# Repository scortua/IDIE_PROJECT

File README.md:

#### Diseño de un Sistema de Monitoreo de Vibraciones IoT con Conectividad LoRaWAN
# PROYECTO INTEGRACIÓN DISPOSITIVOS ELECTRÓNICOS

## Índice
* [PCB](#diseño-pcb)
* [3D](#diseño-3d)

## Entregables del Proyecto

### Entregable 1: Documentación Técnica y Conceptual
La guía se encuentra en el archivo _Markdown_ [Base entregable 1](./ent1.md) y abarca:
- **Introducción:** Presentación del proyecto, la motivación y los objetivos.
- **Detalle del Producto:** Especificaciones técnicas, características físicas y funcionales del dispositivo IoT.
- **Alcance de los Servicios Ofertados:** Descripción de los servicios incluidos, como el diseño de hardware, firmware, pruebas y documentación completa.
- **Exclusiones del Alcance:** Elementos y servicios que no se consideran en el proyecto (producción en masa, logística, etc.).
- **Valor:** Análisis de costos, desglose de inversión y metodologías de cálculo.
- **Cronograma de Trabajo:** Fases del proyecto y tiempo estimado para cada etapa.
- **Tiempo de Entrega:** Fechas clave y plazos para los entregables parciales y finales.

---

### Entregable 2: Diseño y Sustentación Técnica
Disponible en el archivo _Markdown_ [Base entregable 2](./ent2.md), este entregable se compone de:
- **Sustentación del Diseño:** Presentación y defensa del diseño, representando un 30% de la evaluación.
- **Informe Digital Detallado (35%):**
  - Descripción general de la solución y su justificación.
  - Diagramas de bloques que ilustren el flujo y la estructura de la solución.
  - Descripción detallada de cada bloque (funciones y relaciones).
  - Relación entre la solución y los requerimientos solicitados.
  - Especificaciones técnicas de los componentes electrónicos clave (MCU, memorias, fuentes, interfaces, etc.).
  - Diseño esquemático del sistema.
  - Diseño de PCB, presentando cada capa (máscara de componentes, anti-soldadura, crema, cobre y perforaciones).
  - Lista de materiales (BOM List).
  - Modelo 3D del producto final.
  - Cuadro de costos de producción para diferentes volúmenes (1, 10, 100, 500, 1000 y 5000 unidades).
- **Paquete Digital Adicional (35%):**
  - Informe en PDF con toda la documentación.
  - Archivo PDF del esquemático.
  - Archivos GERBER del diseño de la PCB.
  - Archivo BOM en Excel.
  - Archivo STEP o STL del modelo 3D.
  - Hoja de cálculo para el cuadro de costos, con fórmula automática según la cantidad a producir.
  - Hojas de datos (datasheets) de los componentes principales.

---

### Entregable 3: Manuales, Brochure y Prototipo Final
La guía se encuentra en [Base entregable 3](./ent3.md) y comprende:
- **Manual de Usuario:** Documento PDF que explica el funcionamiento y manejo del dispositivo (10%).
- **Brochure del Producto:** Ficha comercial en PDF que resalta las ventajas competitivas y características principales (10%).
- **Informe Digital Actualizado (20%):**
  - Descripción del firmware desarrollado y su funcionamiento.
  - Diagrama de flujo de la aplicación.
  - Detalle de los drivers implementados.
  - Retos y dificultades enfrentadas junto con las soluciones aplicadas.
  - Conclusiones finales y lecciones aprendidas.
  - Inclusión y actualización del paquete digital definido en el Entregable 2.
- **Prototipo Final Funcional:** Durante la presentación, se evaluarán todas las características y funcionalidades estipuladas en el proyecto (60%).

Cada uno de estos entregables está diseñado para garantizar una documentación integral y una validación exhaustiva del proyecto, cubriendo desde la concepción de la idea hasta la demostración práctica del sistema IoT.

# DISEÑO GENERAL
Antes de comenzar es necesario buscar sobre dispositivos similares y si existen, toda la idea de los componentes principales que tienen sus características principales en el diseño y después los requeridos para el funcionamiento de lo necesario.

## Diseño PCB

<details>
<summary> Dimensiones </summary>
Primer paso fue construir la PCB que entrara a la perfección dentro de la caja seleccionada que se ve a continuación.

Estas medidas se siguieron al pie de la letra para poder diseñar a la perfección la PCB y el circuito que se desea.
</details>

## Componentes
#### Componentes Usados

A continuación se describen los dispositivos fundamentales utilizados en el proyecto, documentados en los archivos PDF disponibles:

- **Socket Batería:** ([1015-socketbattery.pdf](./Documentos/1015-socketbattery.pdf))  
  Se especifica el diseño del conector para integración segura y confiable del paquete de alimentación.

- **Cristal Oscilador:** ([ABS06-cristal.pdf](./Documentos/ABS06-cristal.pdf))  
  Fundamental para la sincronización de circuitos, garantizando estabilidad y precisión en el reloj del sistema.

- **Bobina y Núcleo de Ferrita:** ([core_ferrita-coil.pdf](./Documentos/core_ferrita-coil.pdf))  
  Componentes críticos en la filtración y manejo de interferencias electromagnéticas en el circuito.

- **Convertidor Serial:** ([DS_FT234XD-serialconverter.pdf](./Documentos/DS_FT234XD-serialconverter.pdf))  
  Facilita la comunicación entre el microcontrolador y dispositivos externos mediante interfaces USB y serie.

- **Unidad de Medición Inercial (IMU):** ([FXLS8974CFR3-imu.pdf](./Documentos/FXLS8974CFR3-imu.pdf))  
  Incorpora sensores que permiten la detección y el análisis de movimientos y vibraciones, contribuyendo a la monitorización del estado del dispositivo.

- **Sensor de Efecto Hall:** ([hall_efect-sensor.pdf](./Documentos/hall_efect-sensor.pdf))  
  Utilizado para detectar cambios en campos magnéticos, lo que aporta datos relevantes en aplicaciones de control de propiedad magnética.

- **LED RGB:** ([HB_CLY6D-rgb_led.pdf](./Documentos/HB_CLY6D-rgb_led.pdf))  
  Proporciona indicadores visuales para el estado del sistema, útil para diagnósticos o notificaciones.

- **Módulo LoRa:** ([LoRa_E5_module.pdf](./Documentos/LoRa_E5_module.pdf))  
  Es el componente clave para la conexión IoT a través de la red LoRaWAN, permitiendo la transmisión de datos a larga distancia.

- **Transistor y MOSFET:** ([transistor.pdf](./Documentos/transistor.pdf), [SI2305B_SOT_23-mosfet.pdf](./Documentos/SI2305B_SOT_23-mosfet.pdf))  
  Empleados para la gestión de señales y el control de potencia dentro del circuito integrado.

- **Microcontrolador:** ([stm32l071v8-micro.pdf](./Documentos/stm32l071v8-micro.pdf))  
  El cerebro del sistema, encargado de coordinar las comunicaciones, procesar las señales de los sensores y gestionar las acciones del dispositivo.

- **Protección de Diodos:** ([usblc6_2SY6-diode-protection.pdf](./Documentos/usblc6_2SY6-diode-protection.pdf))  
  Asegura la integridad del circuito frente a sobretensiones y otros picos de corriente, protegiendo los componentes sensibles.

- **Antena:** ([W2311-antenna.pdf](./Documentos/W2311-antenna.pdf))
  La antena es un componente crítico en la conexión IoT a través de LoRaWAN. Su función es asegurar una comunicación fiable y de largo alcance al transmitir y recibir datos en frecuencias específicas.
  - **Tipo:** Diseñada para ser compacta y eficiente, comúnmente usando tecnología PCB o de hilo.
  - **Frecuencia Operativa:** Se adapta a bandas como 433 MHz, 868 MHz o 915 MHz, según las normativas locales.
  - **Ganancia y Eficiencia:** Optimizada para maximizar el alcance y garantizar una recepción estable.

## Esquemático
### Desarrollo del Esquemático

Para el desarrollo del esquemático se utilizó el software Eagle, lo que permitió integrar de forma precisa todos los elementos del circuito. Los componentes se seleccionaron desde Mouser y se incorporaron mediante el gestor de librerías Library Loader, asegurando una integración coherente y validada antes de avanzar al diseño de PCB.
Para la hoja 1 se tiene:

Y para la hoja 2 se tiene:

## PCB
Ahora, con el diseño del esquemático como se planteo es construirlo en un modelo de caja

## Diseño 3D

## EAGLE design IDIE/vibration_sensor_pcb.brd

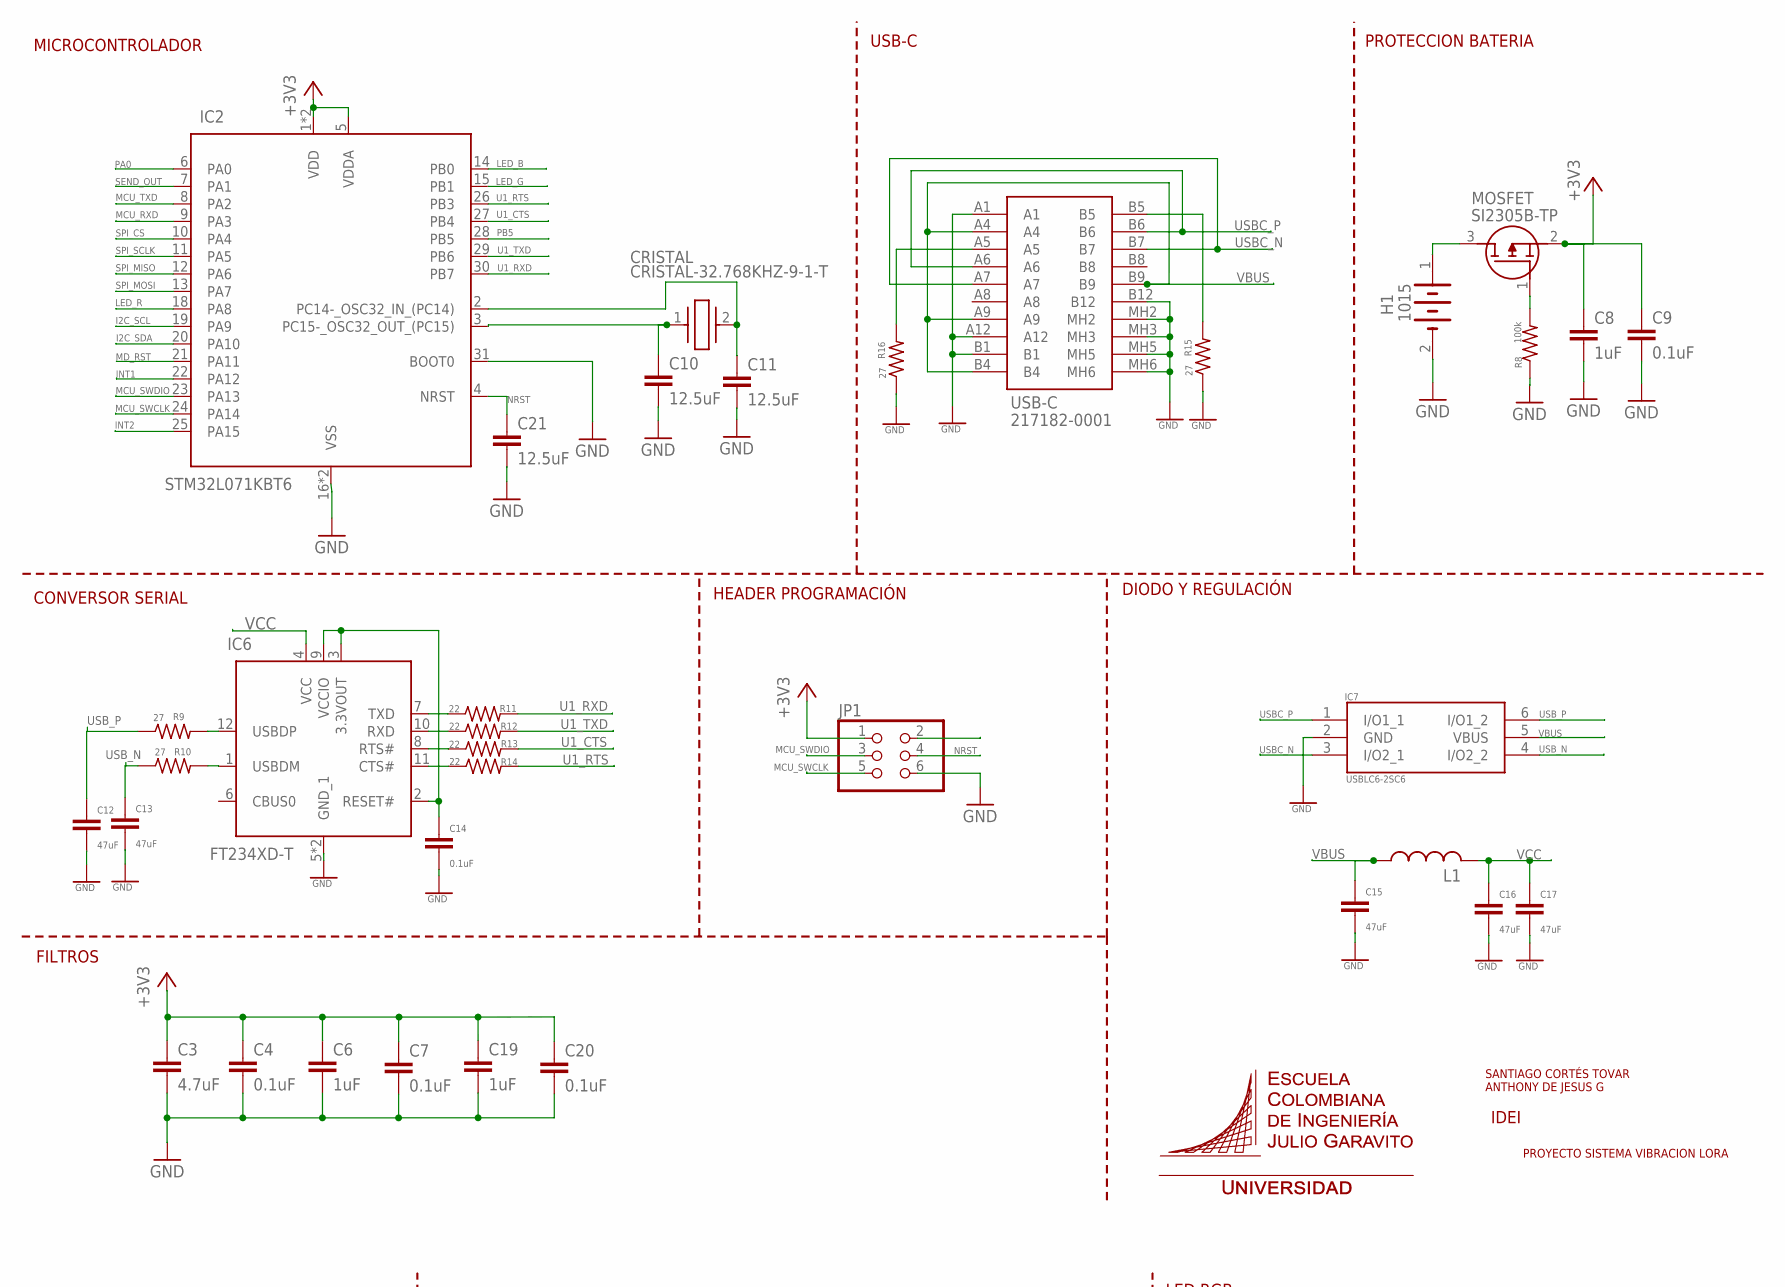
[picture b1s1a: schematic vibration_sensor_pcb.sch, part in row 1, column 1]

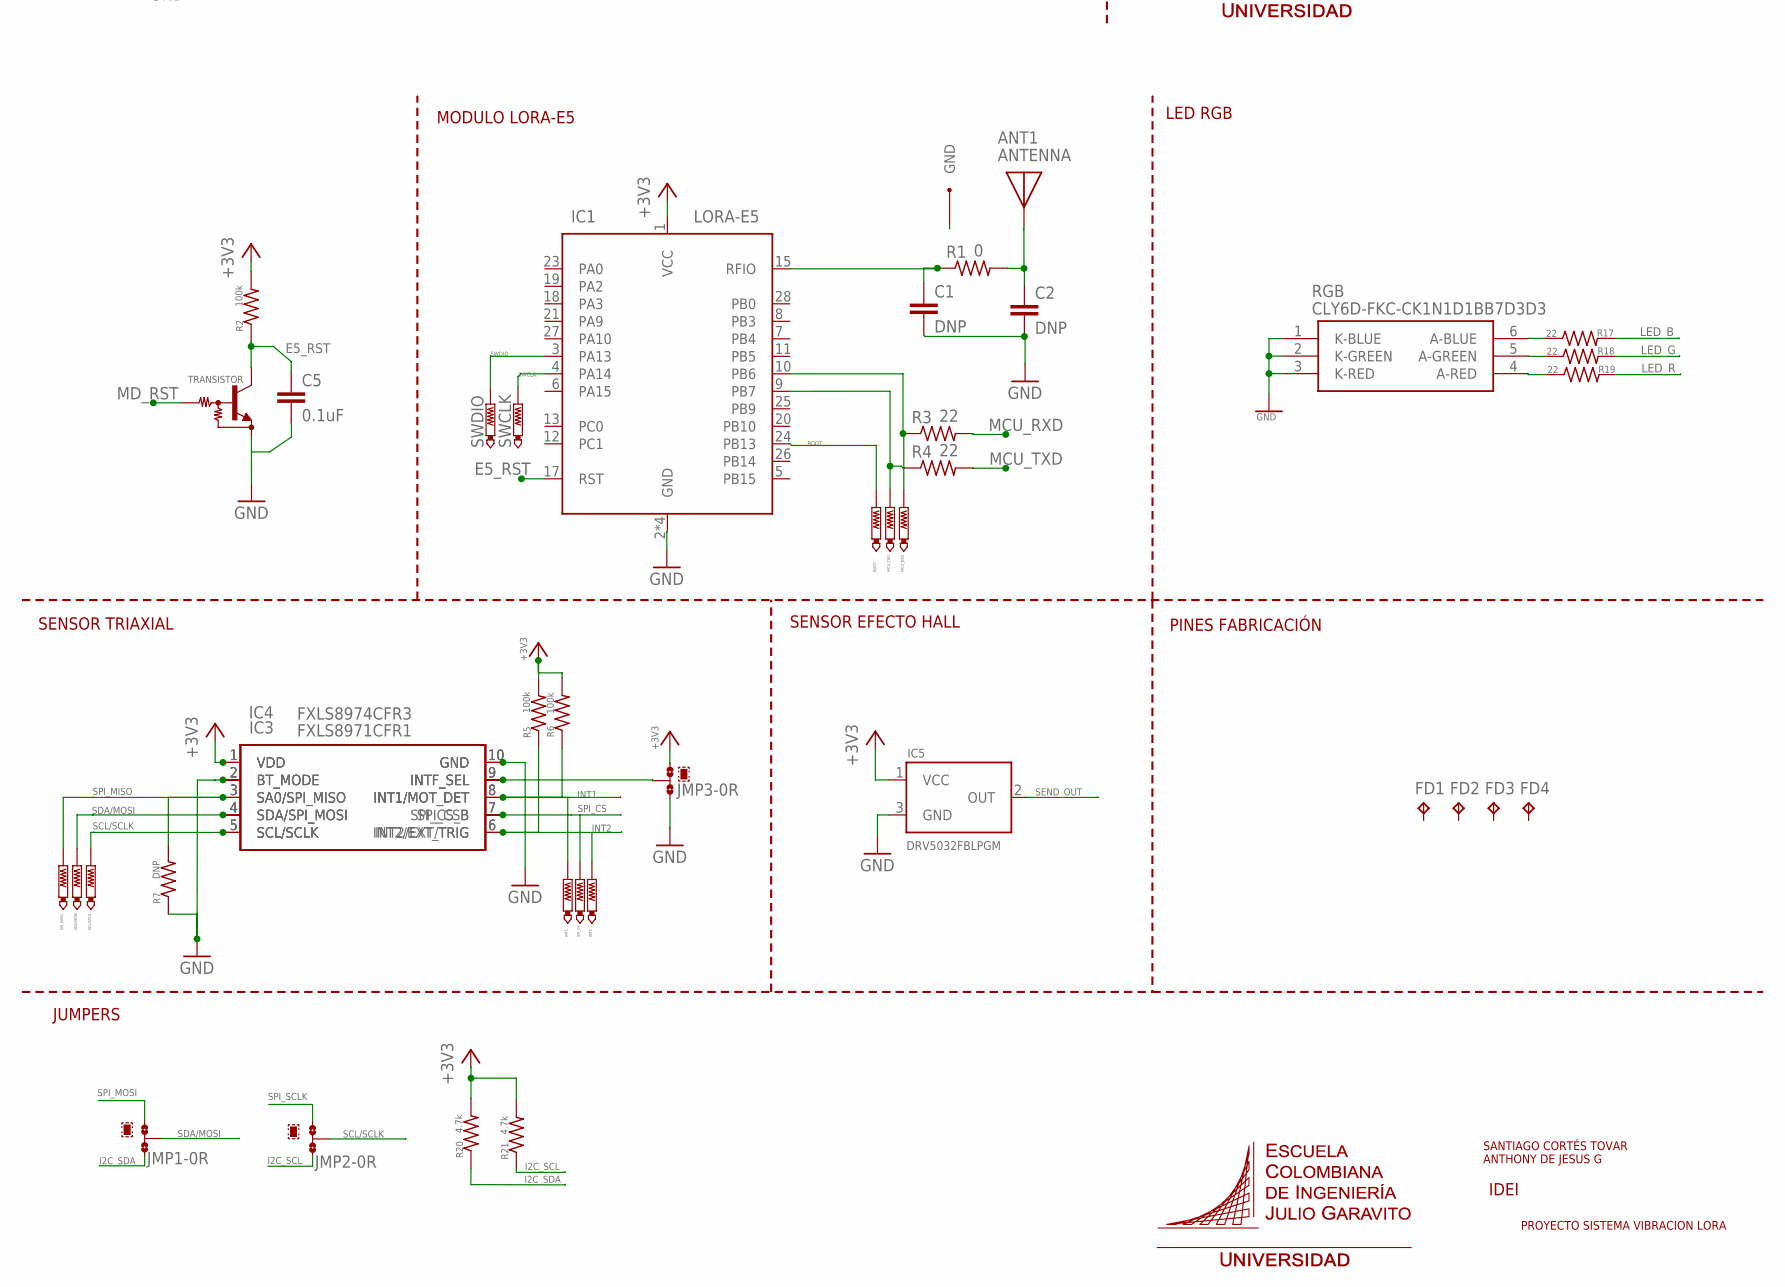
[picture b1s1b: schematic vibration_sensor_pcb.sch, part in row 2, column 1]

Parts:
ANT1: ANTENNA
BOOT: PTR1TP11R; TP11R
C1, C2: DNP; C0603
C3: 4.7uF; C0603
C4, C5, C7, C9, C14, C20: 0.1uF; C0603
C6, C8, C19: 1uF; C0603
C10, C11, C21: 12.5uF; C0603
C12, C13, C15, C16, C17: 47uF; C0603
CRISTAL: CRISTAL-32.768KHZ-9-1-T; CRISTAL-32.768
FD1, FD2, FD3, FD4: TPTP10R; TP10R
H1: 1015
IC1: LORA-E5
IC2: STM32L071KBT6
IC3: FXLS8974CFR3
IC4: FXLS8971CFR1
IC5: DRV5032FBLPGM; SOT23
IC6: FT234XD-T; SON45P300X300X80-13N
IC7: USBLC6-2SC6; SOT95P280X145-6N
INT1, INT2: PTR1TP11R; TP11R
JMP1, JMP2, JMP3: 0R-JUMPA; A0R-JMP
JP1: PINHD-2X3; 2X03
L1: L-US; C0805K
MCU_RXD: PTR1TP11R; TP11R
MCU_TXD: PTR1TP11R; TP11R
MOSFET: SI2305B-TP; SOT95P237X125-3N
R1: 0; R0603
R2, R5, R6, R8: 100k; R0603
R3, R4, R11, R12, R13, R14, R17, R18, R19: 22; R0603
R7: DNP; R0603
R9, R10, R15, R16: 27; R0603
R20, R21: 4.7k; R0603
RGB: CLY6D-FKC-CK1N1D1BB7D3D3; PLCC6
SCL/SCLK: PTR1TP11R; TP11R
SDA/MOSI: PTR1TP11R; TP11R
SPI_CS: PTR1TP11R; TP11R
SPI_MISO: PTR1TP11R; TP11R
SWCLK: PTR1TP11R; TP11R
SWDIO: PTR1TP11R; TP11R
TRANSISTOR: MUN2211T1-NPN_DRIVER-SC59-BEC; SC59-BEC
USB-C: 217182-0001; 2171820001

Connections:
+3V3: C3.1, C4.1, C6.1, C7.1, C8.1, C9.1, C19.1, C20.1, IC1.1 (VCC), IC2.1 (VDD), IC2.5 (VDDA), IC2.17 (VDD), IC3.1 (VDD), IC4.1 (VDD), IC5.1 (VCC), JMP3.3, JP1.1, MOSFET.2 (S), R2.2, R5.2, R6.2, R20.2, R21.2
A5: R16.2, USB-C.A5
ANT: ANT1.1 (FEED), C2.1, R1.2
B5: R15.2, USB-C.B5
BOOT: BOOT.TP, IC1.24 (PB13)
E5_RST: C5.1, IC1.17 (RST), R2.1, TRANSISTOR.C
GATE: MOSFET.1 (G), R8.2
GND: ANT1.2 (GND), ANT1.3 (GND), C1.2, C2.2, C3.2, C4.2, C5.2, C6.2, C7.2, C8.2, C9.2, C10.2, C11.2, C12.2, C13.2, C14.2, C15.2, C16.2, C17.2, C19.2, C21.2, H1.2 (-), IC1.2 (GND), IC1.14 (GND), IC1.16 (GND), IC1.22 (GND), IC2.16 (VSS), IC2.31 (BOOT0), IC2.32 (VSS), IC3.2 (BT_MODE), IC3.10 (GND), IC4.2 (BT_MODE), IC4.10 (GND), IC5.3 (GND), IC6.5 (GND_1), IC6.13 (GND_1), IC7.2 (GND), JMP3.1, JP1.6, R7.1, R8.1, R15.1, R16.1, RGB.1 (K-BLUE), RGB.2 (K-GREEN), RGB.3 (K-RED), TRANSISTOR.E, USB-C.A1, USB-C.A12, USB-C.B1, USB-C.B12, USB-C.MH2, USB-C.MH3, USB-C.MH5, USB-C.MH6
GND1: C20.2
I2C_SCL: IC2.19 (PA9), JMP2.3, R21.1
I2C_SDA: IC2.20 (PA10), JMP1.3, R20.1
INT1: IC2.22 (PA12), IC3.8 (INT1/MOT_DET), IC4.8 (INT1/MOT_DET), INT1.TP, R6.1
INT2: IC2.25 (PA15), IC3.6 (INT2/EXT_TRIG), IC4.6 (INT2/EXT/TRIG), INT2.TP, R5.1
INTF_SEL: IC3.9 (INTF_SEL), IC4.9 (INTF_SEL), JMP3.2
IN_MOSFET: H1.1 (+), MOSFET.3 (D)
LED_B: IC2.14 (PB0), R17.2
LED_G: IC2.15 (PB1), R18.2
LED_R: IC2.18 (PA8), R19.2
LORA_RXD: IC1.10 (PB6), MCU_RXD.TP, R3.1
LORA_TXD: IC1.9 (PB7), MCU_TXD.TP, R4.1
MCU_RXD: IC2.9 (PA3), R3.2
MCU_SWCLK: IC2.24 (PA14), JP1.5
MCU_SWDIO: IC2.23 (PA13), JP1.3
MCU_TXD: IC2.8 (PA2), R4.2
MD_RST: IC2.21 (PA11), TRANSISTOR.B
NRST: C21.1, IC2.4 (NRST), JP1.4
OSC32_IN: C11.1, CRISTAL.2, IC2.2 (PC14-_OSC32_IN_(PC14))
OSC32_OUT: C10.1, CRISTAL.1, IC2.3 (PC15-_OSC32_OUT_(PC15))
OUT_ANT: C1.1, IC1.15 (RFIO), R1.1
PA0: IC2.6 (PA0)
PB5: IC2.28 (PB5)
R11: IC6.7 (TXD), R11.1
R12: IC6.10 (RXD), R12.1
R13: IC6.8 (RTS#), R13.1
R14: IC6.11 (CTS#), R14.1
R17: R17.1, RGB.6 (A-BLUE)
R18: R18.1, RGB.5 (A-GREEN)
R19: R19.1, RGB.4 (A-RED)
RESET#: C14.1, IC6.2 (RESET#), IC6.3 (3.3VOUT), IC6.9 (VCCIO)
SCL/SCLK: IC3.5 (SCL/SCLK), IC4.5 (SCL/SCLK), JMP2.2, SCL/SCLK.TP
SDA/MOSI: IC3.4 (SDA/SPI_MOSI), IC4.4 (SDA/SPI_MOSI), JMP1.2, SDA/MOSI.TP
SEND_OUT: IC2.7 (PA1), IC5.2 (OUT)
SPI_CS: IC2.10 (PA4), IC3.7 (SPI_CS_B), IC4.7 (SPI_CSB), SPI_CS.TP
SPI_MISO: IC2.12 (PA6), IC3.3 (SA0/SPI_MISO), IC4.3 (SA0/SPI_MISO), R7.2, SPI_MISO.TP
SPI_MOSI: IC2.13 (PA7), JMP1.1
SPI_SCLK: IC2.11 (PA5), JMP2.1
SWCLK: IC1.4 (PA14), SWCLK.TP
SWDIO: IC1.3 (PA13), SWDIO.TP
U1_CTS: IC2.27 (PB4), R13.2
U1_RTS: IC2.26 (PB3), R14.2
U1_RXD: IC2.30 (PB7), R11.2
U1_TXD: IC2.29 (PB6), R12.2
USBC_N: IC7.3 (I/O2_1), USB-C.A7, USB-C.B7
USBC_P: IC7.1 (I/O1_1), USB-C.A6, USB-C.B6
USBDM: IC6.1 (USBDM), R10.2
USBDP: IC6.12 (USBDP), R9.2
USB_N: C13.1, IC7.4 (I/O2_2), R10.1
USB_P: C12.1, IC7.6 (I/O1_2), R9.1
VBUS: C15.1, IC7.5 (VBUS), L1.1, USB-C.A4, USB-C.A9, USB-C.B4, USB-C.B9
VCC: C16.1, C17.1, IC6.4 (VCC), L1.2

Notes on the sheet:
IDEI
SANTIAGO CORTÉS TOVAR ANTHONY DE JESUS G
PROYECTO SISTEMA VIBRACION LORA
MICROCONTROLADOR
USB-C
PROTECCION BATERIA
CONVERSOR SERIAL
HEADER PROGRAMACIÓN
DIODO Y REGULACIÓN
MODULO LORA-E5
LED RGB
SENSOR TRIAXIAL
SENSOR EFECTO HALL
PINES FABRICACIÓN
JUMPERS
FILTROS

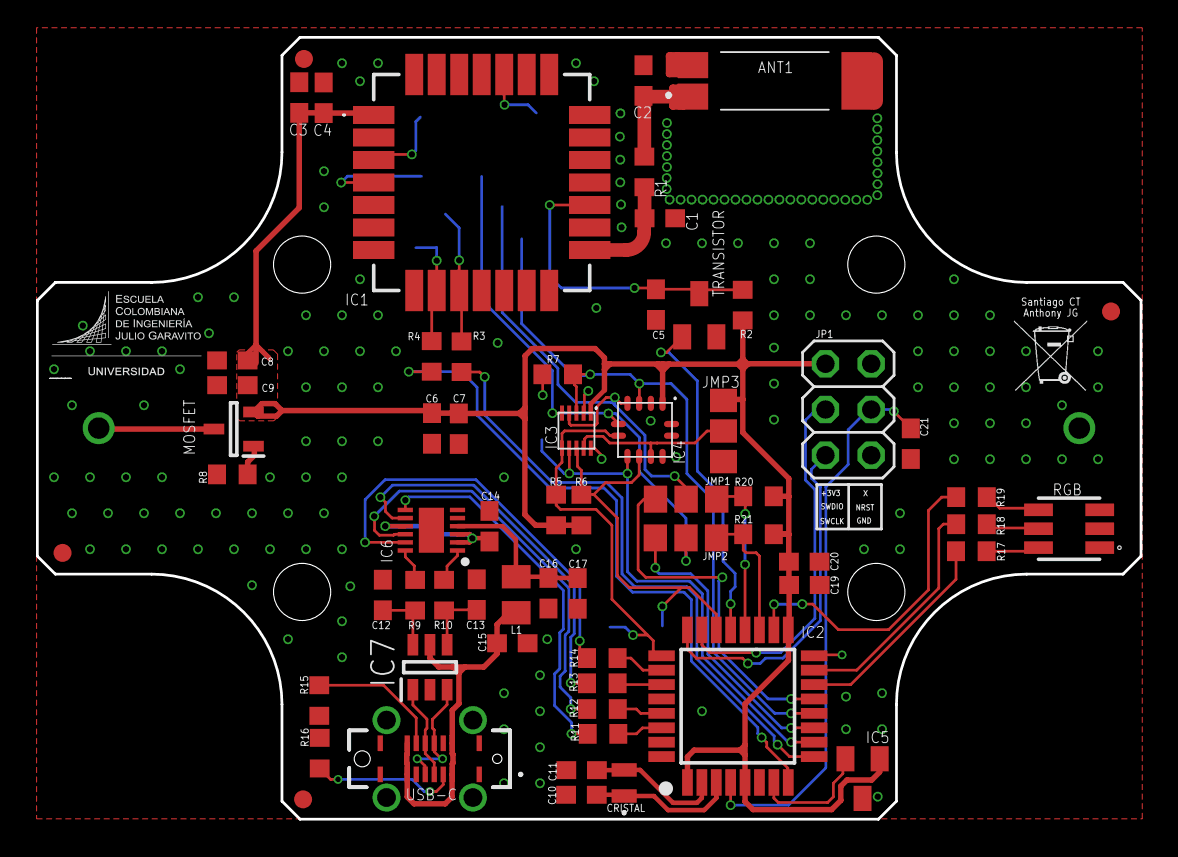
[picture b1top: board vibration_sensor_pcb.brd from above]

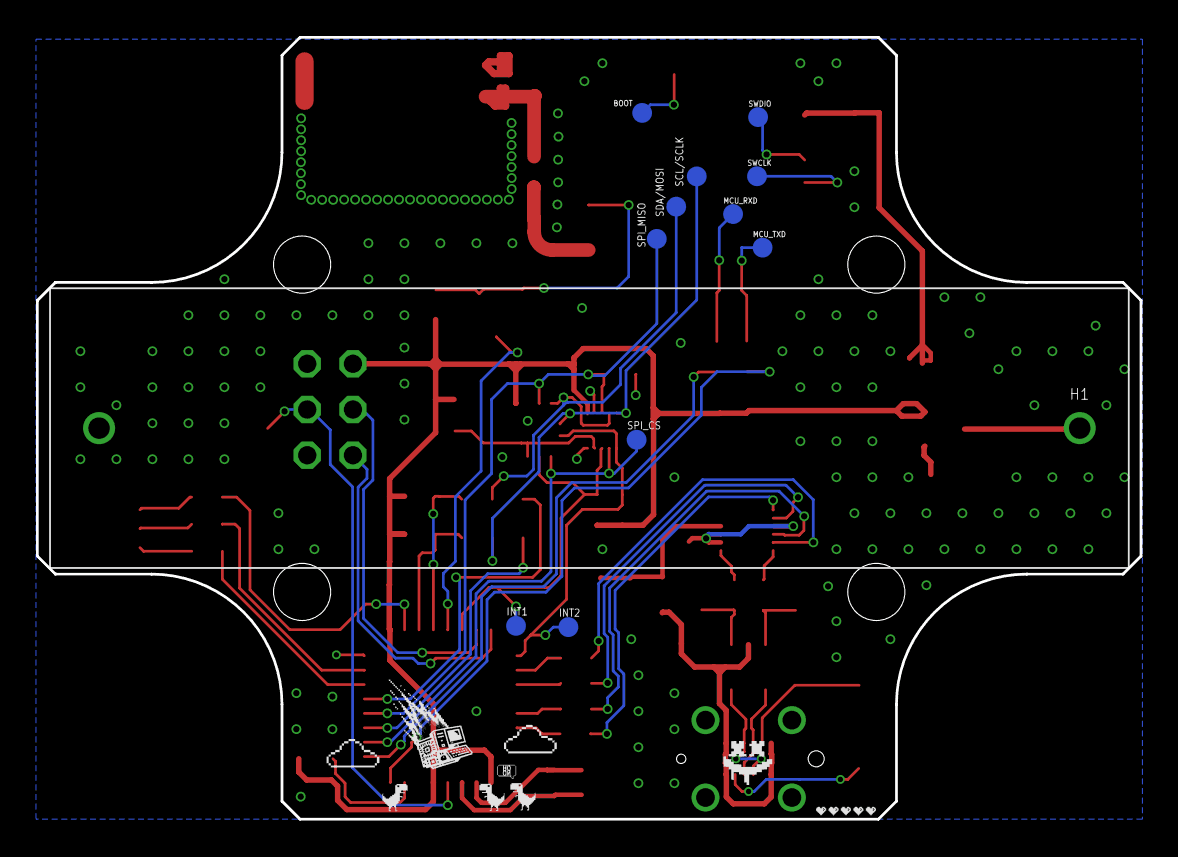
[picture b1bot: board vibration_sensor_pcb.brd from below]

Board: 2 copper layers, 61.3 x 43.4 mm, 75 parts (12 on the bottom side), 57 nets.

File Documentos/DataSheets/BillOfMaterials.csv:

"Qty";"Value";"Device";"Package";"Parts";"Description";"ARROW_PART_NUMBER";"ARROW_PRICE-STOCK";"DESCRIPTION";"HEIGHT";"MANUFACTURER_NAME";"MANUFACTURER_PART_NUMBER";"MOUSER_PART_NUMBER";"MOUSER_PRICE-STOCK";"POPULARITY";"SPICEPREFIX";"TP_SIGNAL_NAME";
"1";"";"L-US";"C0805K";"L1";"INDUCTOR, American symbol";"";"";"";"";"";"";"";"";"";"";"";
"1";"";"MUN2211T1-NPN_DRIVER-SC59-BEC";"SC59-BEC";"TRANSISTOR";"NPN Bias Resistor Transistor";"";"";"";"";"";"";"";"";"0";"J";"";
"1";"";"PINHD-2X3";"2X03";"JP1";"PIN HEADER";"";"";"";"";"";"";"";"";"62";"";"";
"1";"0";"R-US_R0603";"R0603";"R1";"RESISTOR, American symbol";"";"";"";"";"";"";"";"";"77";"R";"";
"6";"0.1uF";"C-EUC0603";"C0603";"C4, C5, C7, C9, C14, C20";"CAPACITOR, European symbol";"";"";"";"";"";"";"";"";"73";"C";"";
"3";"0R-JUMPA";"0R-JUMPA";"A0R-JMP";"JMP1, JMP2, JMP3";"SMD 0R 0805 Jumper";"";"";"";"";"";"";"";"";"3";"";"";
"4";"100k";"R-US_R0603";"R0603";"R2, R5, R6, R8";"RESISTOR, American symbol";"";"";"";"";"";"";"";"";"77";"R";"";
"1";"1015";"1015";"1015";"H1";"Cylindrical Battery Contacts, Clips, Holders & Springs AA PC Battery HOLDER";"";"";"Cylindrical Battery Contacts, Clips, Holders & Springs AA PC Battery HOLDER";"mm";"Keystone Electronics";"1015";"534-1015";"https://www.mouser.co.uk/ProductDetail/Keystone-Electronics/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";"";"";"";
"3";"12.5uF";"C-EUC0603";"C0603";"C10, C11, C21";"CAPACITOR, European symbol";"";"";"";"";"";"";"";"";"73";"C";"";
"3";"1uF";"C-EUC0603";"C0603";"C6, C8, C19";"CAPACITOR, European symbol";"";"";"";"";"";"";"";"";"73";"C";"";
"1";"217182-0001";"217182-0001";"2171820001";"USB-C";"USB-C,VERT SMT,16P 6.40mm HT";"";"";"USB-C,VERT SMT,16P 6.40mm HT";"7.6mm";"Molex";"217182-0001";"538-217182-0001";"https://www.mouser.co.uk/ProductDetail/Molex/217182-0001?qs=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";"";"";"";
"9";"22";"R-US_R0603";"R0603";"R3, R4, R11, R12, R13, R14, R17, R18, R19";"RESISTOR, American symbol";"";"";"";"";"";"";"";"";"77";"R";"";
"4";"27";"R-US_R0603";"R0603";"R9, R10, R15, R16";"RESISTOR, American symbol";"";"";"";"";"";"";"";"";"77";"R";"";
"2";"4.7k";"R-US_R0603";"R0603";"R20, R21";"RESISTOR, American symbol";"";"";"";"";"";"";"";"";"77";"R";"";
"1";"4.7uF";"C-EUC0603";"C0603";"C3";"CAPACITOR, European symbol";"";"";"";"";"";"";"";"";"73";"C";"";
"5";"47uF";"C-EUC0603";"C0603";"C12, C13, C15, C16, C17";"CAPACITOR, European symbol";"";"";"";"";"";"";"";"";"73";"C";"";
"1";"ANTENNA";"ANTENNA";"ANTENNA";"ANT1";"PULSE LARSEN ANTENNAS - W3211 - CERAMIC ON GROUND ANTENNA, 902-928MHZ";"";"";"PULSE LARSEN ANTENNAS - W3211 - CERAMIC ON GROUND ANTENNA, 902-928MHZ";"5mm";"Pulse Electronics";"W3211";"673-W3211";"https://www.mouser.co.uk/ProductDetail/PulseLarsen-Antennas/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";"";"";"";
"1";"CLY6D-FKC-CK1N1D1BB7D3D3";"CLY6D-FKC-CK1N1D1BB7D3D3";"PLCC6";"RGB";"LED  Blue/Green/Red 6-Pin PLCC T/R Cree CLY6D-FKC-CK1N1D1BB7D3D3, CLY6D-FKC Series RGB LED, 480 (Blue) nm, 540 (Green) nm, 624 (Red) nm PLCC 6";"";"";"LED  Blue/Green/Red 6-Pin PLCC T/R Cree CLY6D-FKC-CK1N1D1BB7D3D3, CLY6D-FKC Series RGB LED, 480 (Blue) nm, 540 (Green) nm, 624 (Red) nm PLCC 6";"mm";"CREE LED";"CLY6D-FKC-CK1N1D1BB7D3D3";"941-CLY6DFKCCK1N1D1B";"https://www.mouser.co.uk/ProductDetail/Cree-LED/CLY6D-FKC-CK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";"";"";"";
"1";"CRISTAL-32.768KHZ-9-1-T";"CRISTAL-32.768KHZ-9-1-T";"CRISTAL-32.768";"CRISTAL";"ABRACON - ABS06-32.768KHZ-9-1-T - CRYSTAL, 32.768KHZ, 9PF, 2 X 1.2MM";"";"";"ABRACON - ABS06-32.768KHZ-9-1-T - CRYSTAL, 32.768KHZ, 9PF, 2 X 1.2MM";"0.6mm";"ABRACON";"ABS06-32.768KHZ-9-1-T";"815-ABS06-32.7K-9-T";"https://www.mouser.co.uk/ProductDetail/ABRACON/ABS06-32.768K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";"";"";"";
"2";"DNP";"C-EUC0603";"C0603";"C1, C2";"CAPACITOR, European symbol";"";"";"";"";"";"";"";"";"73";"C";"";
"1";"DNP";"R-US_R0603";"R0603";"R7";"RESISTOR, American symbol";"";"";"";"";"";"";"";"";"77";"R";"";
"1";"DRV5032FBLPGM";"DRV5032FBLPGM";"SOT23";"IC5";"";"";"";"";"";"";"";"";"";"";"";"";
"1";"FT234XD-T";"FT234XD-T";"SON45P300X300X80-13N";"IC6";"USB Interface IC USB to Basic Serial UART IC";"";"";"USB Interface IC USB to Basic Serial UART IC";"0.8mm";"FTDI(Future Designs)";"FT234XD-T";"";"";"";"";"";
"1";"FXLS8971CFR1";"FXLS8971CFR1";"FXLS8971CFR1";"IC4";"3-Axis Low-g Accelerometer FXLS8971CF is available in a 3 mm x 3 mm x 1.25 mm 12-pin QFN package with 0.65 mm pitch and wettable flanks";"";"";"3-Axis Low-g Accelerometer FXLS8971CF is available in a 3 mm x 3 mm x 1.25 mm 12-pin QFN package with 0.65 mm pitch and wettable flanks";"1.3mm";"NXP";"FXLS8971CF";"";"";"";"";"";
"1";"FXLS8974CFR3";"FXLS8974CFR3";"FXLS8974CFR3";"IC3";"Accelerometer X, Y, Z Axis +/-2g, 4g, 8g, 16g 1.6kHz 10-DFN (2x2)";"";"";"Accelerometer X, Y, Z Axis +/-2g, 4g, 8g, 16g 1.6kHz 10-DFN (2x2)";"1mm";"NXP";"FXLS8974CFR3";"771-FXLS8974CFR3";"https://www.mouser.co.uk/ProductDetail/NXP-Semiconductors/FX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";"";"";"";
"1";"LORA-E5";"LORA-E5";"LORA-E5";"IC1";"Sub-GHz Modules LoRa-E5 Wireless Module LoRa-E5 has a 28-pin SMD package";"";"";"Sub-GHz Modules LoRa-E5 Wireless Module LoRa-E5 has a 28-pin SMD package";"2.5mm";"Seeed Studio";"317990687";"713-317990687";"https://www.mouser.co.uk/ProductDetail/Seeed-Studio/31799068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";"";"";"";
"11";"PTR1TP11R";"PTR1TP11R";"TP11R";"BOOT, INT1, INT2, MCU_RXD, MCU_TXD, SCL/SCLK, SDA/MOSI, SPI_CS, SPI_MISO, SWCLK, SWDIO";"TEST PIN";"";"";"";"";"";"";"";"";"1";"";"";
"1";"SI2305B-TP";"SI2305B-TP";"SOT95P237X125-3N";"MOSFET";"P-Channel 20 V 4.2A (Tj) 1.4W Surface Mount SOT-23";"";"";"P-Channel 20 V 4.2A (Tj) 1.4W Surface Mount SOT-23";"1.25mm";"MCC";"SI2305B-TP";"833-SI2305B-TP";"https://www.mouser.co.uk/ProductDetail/Micro-Commercial-Comp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";"";"";"";
"1";"STM32L071KBT6";"STM32L071KBT6";"STM32L071KBT6";"IC2";"MCU 32-bit STM32 ARM Cortex M0+ RISC 128KB Flash 2.5V/3.3V 32-Pin LQFP Tray";"";"";"MCU 32-bit STM32 ARM Cortex M0+ RISC 128KB Flash 2.5V/3.3V 32-Pin LQFP Tray";"1.6mm";"STMicroelectronics";"STM32L071KBT6";"511-STM32L071KBT6";"https://www.mouser.co.uk/ProductDetail/STMicroelectronics/ST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";"";"";"";
"4";"TPTP10R";"TPTP10R";"TP10R";"FD1, FD2, FD3, FD4";"Test pad";"";"";"";"";"";"";"";"";"3";"";"";
"1";"USBLC6-2SC6";"USBLC6-2SC6";"SOT95P280X145-6N";"IC7";"TVS Diode Array Uni-Directional USBLC6-2SC6 17V, SOT-23 6-Pin";"";"";"TVS Diode Array Uni-Directional USBLC6-2SC6 17V, SOT-23 6-Pin";"1.45mm";"STMicroelectronics";"USBLC6-2SC6";"511-USBLC6-2SC6";"https://www.mouser.co.uk/ProductDetail/STMicroelectronics/US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";"";"";"";

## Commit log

2025-02-06 Initial project version
2025-02-06 Firs general commit
2025-02-06 Actualización README y aechivos de interes
2025-02-08 Actualizacion documentos
2025-02-12 update readme with doing in last week
2025-02-15 add and update pcb design with lora, stm, battery
2025-02-16 add new design with other modules
2025-02-18 UPDATE informacion ent1 y diseño pcb y materiales
2025-02-22 ADD documentacion de componentes
2025-03-06 UPLOADING todo el diseño nuevo de pcb con conexiones de spi e i2c
2025-03-11 ADD crista sensor hall
2025-03-19 UPDATE se agregan y conectan componentes de pcb, mosfet, jumpers...
2025-03-19 UPDATE nueva hoja con usb y diversas conecciones antes de ruteo
2025-03-19 UPDATE casi terminacion del diseño, cambiar efecto hall y conectar ruteo
2025-03-27 UPDATE orden de pcb y reglas de diseño
2025-03-28 UPDATE bloques y 3d
2025-03-29 ADD & UPDATE documentacion, modelado 3d y poco ruteo
2025-03-29 UPDATE schematic
2025-03-30 UPDATE schematic and PCB route
2025-04-07 UPDATE pcb schematic
2025-04-10 UPDATE file of the project
2025-04-12 UPDATE pcb
2025-05-30 LAST UPDATE
